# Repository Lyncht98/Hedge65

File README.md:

# Hedge65

Covid hobby learning to design a keyboard PCB with through-hole components

Not finished yet

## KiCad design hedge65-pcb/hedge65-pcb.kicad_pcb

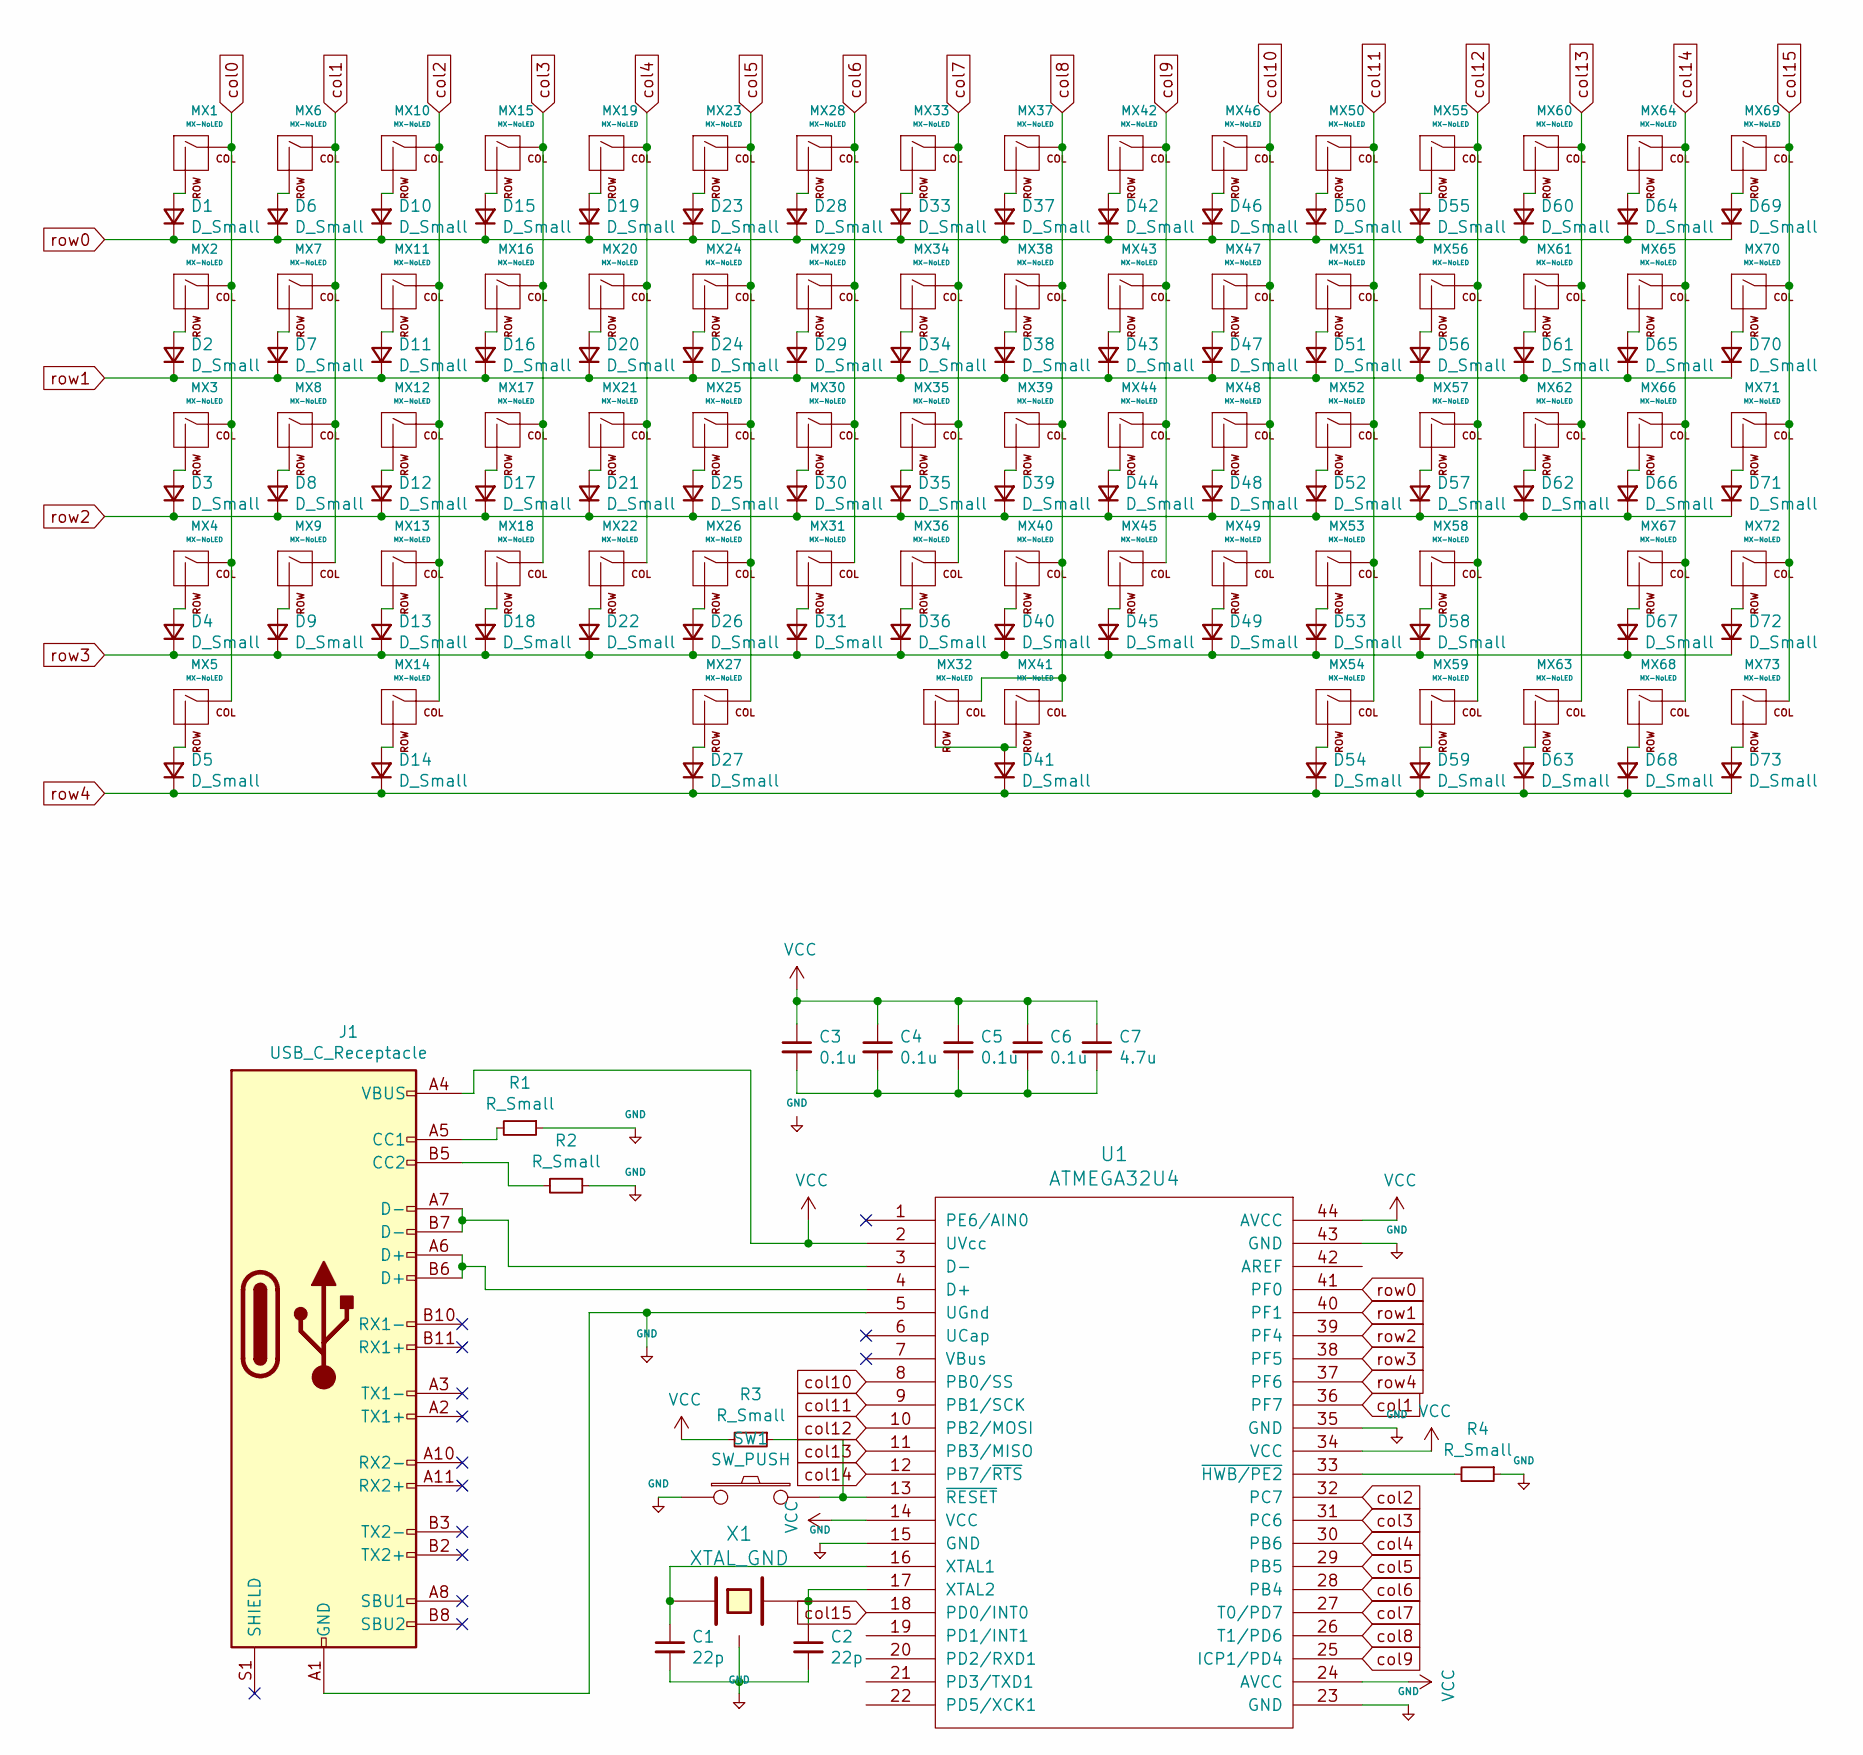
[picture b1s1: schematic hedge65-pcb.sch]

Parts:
C1, C2: 22p; C_0805_2012Metric
C3, C4, C5, C6: 0.1u; C_0805_2012Metric
C7: 4.7u; C_0805_2012Metric
D1, D2, D3, D4, D5, D6, D7, D8, D9, D10, D11, D12, D13, D14, D15, D16, D17, D18, D19, D20, D21, D22, D23, D24, D25, D26, D27, D28, D29, D30, D31, D33, D34, D35, D36, D37, D38, D39, D40, D41, D42, D43, D44, D45, D46, D47, D48, D49, D50, D51, D52, D53, D54, D55, D56, D57, D58, D59, D60, D61, D62, D63, D64, D65, D66, D67, D68, D69, D70, D71, D72, D73: D_Small; D_DO-35_SOD27_P5.08mm_Horizontal
J1: USB_C_Receptacle; USB_C_Receptacle_Amphenol_12401548E4-2A_CircularHoles
MX1, MX2, MX3, MX4, MX5, MX6, MX7, MX8, MX9, MX10, MX11, MX12, MX13, MX14, MX15, MX16, MX17, MX18, MX19, MX20, MX21, MX22, MX23, MX24, MX25, MX26, MX27, MX28, MX29, MX30, MX31, MX32, MX33, MX34, MX35, MX36, MX37, MX38, MX39, MX40, MX41, MX42, MX43, MX44, MX45, MX46, MX47, MX48, MX49, MX50, MX51, MX52, MX53, MX54, MX55, MX56, MX57, MX58, MX59, MX60, MX61, MX62, MX63, MX64, MX65, MX66, MX67, MX68, MX69, MX70, MX71, MX72, MX73: MX-NoLED; MX-1U-NoLED
R1, R2, R3, R4: R_Small; R_0805_2012Metric
SW1: SW_PUSH; SKQG-1155865
U1: ATMEGA32U4; ATmega32U4
X1: XTAL_GND; Crystal_SMD_3225-4Pin_3.2x2.5mm

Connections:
+5V: C1.2, C2.2, J1.A1 (GND), J1.A12 (GND), J1.B1 (GND), J1.B12 (GND), R1.1, R2.1, R4.1, SW1.1, U1.5 (UGnd), U1.15 (GND), U1.23 (GND), U1.35 (GND), U1.43 (GND), X1.3
unnamed: C1.1, U1.16 (XTAL1), X1.1
unnamed: C2.1, U1.17 (XTAL2), X1.2
unnamed: C3.2, C4.2, C5.2, C6.2, C7.2
unnamed: D1.2 (A), MX1.2 (ROW)
unnamed: D2.2 (A), MX2.2 (ROW)
unnamed: D3.2 (A), MX3.2 (ROW)
unnamed: D4.2 (A), MX4.2 (ROW)
unnamed: D5.2 (A), MX5.2 (ROW)
unnamed: D6.2 (A), MX6.2 (ROW)
unnamed: D7.2 (A), MX7.2 (ROW)
unnamed: D8.2 (A), MX8.2 (ROW)
unnamed: D9.2 (A), MX9.2 (ROW)
unnamed: D10.2 (A), MX10.2 (ROW)
unnamed: D11.2 (A), MX11.2 (ROW)
unnamed: D12.2 (A), MX12.2 (ROW)
unnamed: D13.2 (A), MX13.2 (ROW)
unnamed: D14.2 (A), MX14.2 (ROW)
unnamed: D15.2 (A), MX15.2 (ROW)
unnamed: D16.2 (A), MX16.2 (ROW)
unnamed: D17.2 (A), MX17.2 (ROW)
unnamed: D18.2 (A), MX18.2 (ROW)
unnamed: D19.2 (A), MX19.2 (ROW)
unnamed: D20.2 (A), MX20.2 (ROW)
unnamed: D21.2 (A), MX21.2 (ROW)
unnamed: D22.2 (A), MX22.2 (ROW)
unnamed: D23.2 (A), MX23.2 (ROW)
unnamed: D24.2 (A), MX24.2 (ROW)
unnamed: D25.2 (A), MX25.2 (ROW)
unnamed: D26.2 (A), MX26.2 (ROW)
unnamed: D27.2 (A), MX27.2 (ROW)
unnamed: D28.2 (A), MX28.2 (ROW)
unnamed: D29.2 (A), MX29.2 (ROW)
unnamed: D30.2 (A), MX30.2 (ROW)
unnamed: D31.2 (A), MX31.2 (ROW)
unnamed: D33.2 (A), MX33.2 (ROW)
unnamed: D34.2 (A), MX34.2 (ROW)
unnamed: D35.2 (A), MX35.2 (ROW)
unnamed: D36.2 (A), MX36.2 (ROW)
unnamed: D37.2 (A), MX37.2 (ROW)
unnamed: D38.2 (A), MX38.2 (ROW)
unnamed: D39.2 (A), MX39.2 (ROW)
unnamed: D40.2 (A), MX40.2 (ROW)
unnamed: D41.2 (A), MX32.2 (ROW), MX41.2 (ROW)
unnamed: D42.2 (A), MX42.2 (ROW)
unnamed: D43.2 (A), MX43.2 (ROW)
unnamed: D44.2 (A), MX44.2 (ROW)
unnamed: D45.2 (A), MX45.2 (ROW)
unnamed: D46.2 (A), MX46.2 (ROW)
unnamed: D47.2 (A), MX47.2 (ROW)
unnamed: D48.2 (A), MX48.2 (ROW)
unnamed: D49.2 (A), MX49.2 (ROW)
unnamed: D50.2 (A), MX50.2 (ROW)
unnamed: D51.2 (A), MX51.2 (ROW)
unnamed: D52.2 (A), MX52.2 (ROW)
unnamed: D53.2 (A), MX53.2 (ROW)
unnamed: D54.2 (A), MX54.2 (ROW)
unnamed: D55.2 (A), MX55.2 (ROW)
unnamed: D56.2 (A), MX56.2 (ROW)
unnamed: D57.2 (A), MX57.2 (ROW)
unnamed: D58.2 (A), MX58.2 (ROW)
unnamed: D59.2 (A), MX59.2 (ROW)
unnamed: D60.2 (A), MX60.2 (ROW)
unnamed: D61.2 (A), MX61.2 (ROW)
unnamed: D62.2 (A), MX62.2 (ROW)
unnamed: D63.2 (A), MX63.2 (ROW)
unnamed: D64.2 (A), MX64.2 (ROW)
unnamed: D65.2 (A), MX65.2 (ROW)
unnamed: D66.2 (A), MX66.2 (ROW)
unnamed: D67.2 (A), MX67.2 (ROW)
unnamed: D68.2 (A), MX68.2 (ROW)
unnamed: D69.2 (A), MX69.2 (ROW)
unnamed: D70.2 (A), MX70.2 (ROW)
unnamed: D71.2 (A), MX71.2 (ROW)
unnamed: D72.2 (A), MX72.2 (ROW)
unnamed: D73.2 (A), MX73.2 (ROW)
unnamed: J1.A5 (CC1), R1.2
unnamed: J1.A6 (D+), J1.B6 (D+), U1.4 (D+)
unnamed: J1.A7 (D-), J1.B7 (D-), U1.3 (D-)
unnamed: J1.B5 (CC2), R2.2
unnamed: R3.1, SW1.2, U1.13 (~RESET)
unnamed: R4.2, U1.33 (~HWB/PE2)
VCC: C3.1, C4.1, C5.1, C6.1, C7.1, J1.A4 (VBUS), J1.A9 (VBUS), J1.B4 (VBUS), J1.B9 (VBUS), R3.2, U1.2 (UVcc), U1.14 (VCC), U1.24 (AVCC), U1.34 (VCC), U1.44 (AVCC)
col0: MX1.1 (COL), MX2.1 (COL), MX3.1 (COL), MX4.1 (COL), MX5.1 (COL)
col1: MX6.1 (COL), MX7.1 (COL), MX8.1 (COL), MX9.1 (COL), U1.36 (PF7)
col2: MX10.1 (COL), MX11.1 (COL), MX12.1 (COL), MX13.1 (COL), MX14.1 (COL), U1.32 (PC7)
col3: MX15.1 (COL), MX16.1 (COL), MX17.1 (COL), MX18.1 (COL), U1.31 (PC6)
col4: MX19.1 (COL), MX20.1 (COL), MX21.1 (COL), MX22.1 (COL), U1.30 (PB6)
col5: MX23.1 (COL), MX24.1 (COL), MX25.1 (COL), MX26.1 (COL), MX27.1 (COL), U1.29 (PB5)
col6: MX28.1 (COL), MX29.1 (COL), MX30.1 (COL), MX31.1 (COL), U1.28 (PB4)
col7: MX33.1 (COL), MX34.1 (COL), MX35.1 (COL), MX36.1 (COL), U1.27 (T0/PD7)
col8: MX32.1 (COL), MX37.1 (COL), MX38.1 (COL), MX39.1 (COL), MX40.1 (COL), MX41.1 (COL), U1.26 (T1/PD6)
col9: MX42.1 (COL), MX43.1 (COL), MX44.1 (COL), MX45.1 (COL), U1.25 (ICP1/PD4)
col10: MX46.1 (COL), MX47.1 (COL), MX48.1 (COL), MX49.1 (COL), U1.8 (PB0/SS)
col11: MX50.1 (COL), MX51.1 (COL), MX52.1 (COL), MX53.1 (COL), MX54.1 (COL), U1.9 (PB1/SCK)
col12: MX55.1 (COL), MX56.1 (COL), MX57.1 (COL), MX58.1 (COL), MX59.1 (COL), U1.10 (PB2/MOSI)
col13: MX60.1 (COL), MX61.1 (COL), MX62.1 (COL), MX63.1 (COL), U1.11 (PB3/MISO)
col14: MX64.1 (COL), MX65.1 (COL), MX66.1 (COL), MX67.1 (COL), MX68.1 (COL), U1.12 (PB7/~RTS)
col15: MX69.1 (COL), MX70.1 (COL), MX71.1 (COL), MX72.1 (COL), MX73.1 (COL), U1.18 (PD0/INT0)
row0: D1.1 (K), D6.1 (K), D10.1 (K), D15.1 (K), D19.1 (K), D23.1 (K), D28.1 (K), D33.1 (K), D37.1 (K), D42.1 (K), D46.1 (K), D50.1 (K), D55.1 (K), D60.1 (K), D64.1 (K), D69.1 (K), U1.41 (PF0)
row1: D2.1 (K), D7.1 (K), D11.1 (K), D16.1 (K), D20.1 (K), D24.1 (K), D29.1 (K), D34.1 (K), D38.1 (K), D43.1 (K), D47.1 (K), D51.1 (K), D56.1 (K), D61.1 (K), D65.1 (K), D70.1 (K), U1.40 (PF1)
row2: D3.1 (K), D8.1 (K), D12.1 (K), D17.1 (K), D21.1 (K), D25.1 (K), D30.1 (K), D35.1 (K), D39.1 (K), D44.1 (K), D48.1 (K), D52.1 (K), D57.1 (K), D62.1 (K), D66.1 (K), D71.1 (K), U1.39 (PF4)
row3: D4.1 (K), D9.1 (K), D13.1 (K), D18.1 (K), D22.1 (K), D26.1 (K), D31.1 (K), D36.1 (K), D40.1 (K), D45.1 (K), D49.1 (K), D53.1 (K), D58.1 (K), D67.1 (K), D72.1 (K), U1.38 (PF5)
row4: D5.1 (K), D14.1 (K), D27.1 (K), D41.1 (K), D54.1 (K), D59.1 (K), D63.1 (K), D68.1 (K), D73.1 (K), U1.37 (PF6)

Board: 2 copper layers, 160 parts (0 on the bottom side), 104 nets, no tracks yet.

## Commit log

2020-12-30 set-up
2020-12-30 added library
2021-01-01 none
2021-01-01 mappings
2021-01-01 schematic done
2021-01-01 pcb laid out
2021-01-01 attached diodes
2021-01-02 redo
2021-01-02 doides shifted to deadspace
2021-01-02 doides all flipped to 225
2021-01-02 diodes like cftkb
2021-01-03 checkpoint idk
2021-01-03 diodes at 245, perfect
